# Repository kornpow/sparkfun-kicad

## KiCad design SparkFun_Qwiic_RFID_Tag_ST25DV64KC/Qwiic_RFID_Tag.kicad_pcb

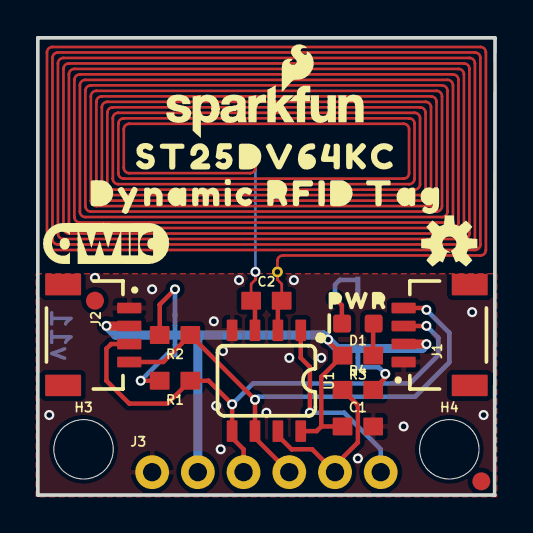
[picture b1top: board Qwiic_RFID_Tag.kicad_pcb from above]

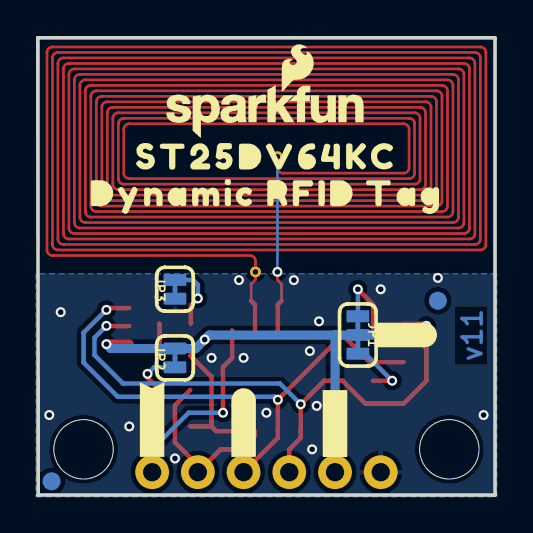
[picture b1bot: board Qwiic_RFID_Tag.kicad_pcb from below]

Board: 2 copper layers, 25.4 x 25.4 mm, 40 parts (17 on the bottom side), 13 nets.

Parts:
C1: 0.1uF; 0603
C2: 4.7pF; 0603
D1: RED; LED-0603
FD1, FD2, FD3, FD4: FIDUCIAL1X2; FIDUCIAL-1X2
FRAME2: FRAME-LETTER; CREATIVE_COMMONS
H3, H4: STAND-OFF
J1, J2: Qwiic; JST04_1MM_RA
J3: 1X06_NO_SILK
JP1: JUMPER-SMT_3_2-NC_TRACE_SILK; SMT-JUMPER_3_2-NC_TRACE_SILK
JP2, JP3: JUMPER-SMT_2_NC_TRACE_SILK; SMT-JUMPER_2_NC_TRACE_SILK
L1: PCB_4UH_INDUCTOR-1X0.5; PCB_4UH_INDUCTOR_1X0.5
LOGO1: OSHW-LOGOS; OSHW-LOGO-S
LOGO2, LOGO4: SFE_LOGO_NAME_FLAME.1_INCH; SFE_LOGO_NAME_FLAME_.1
LOGO3: QWIIC_LOGO_7MM; QWIIC_7MM
R1, R2: 2.2k; 0603
R3: 1k; 0603
R4: 10k; 0603
U1: ST25DV64KC; SO08
U$1: #I2C#0
U$3: #3V3#0
U$9: PWR11
U$10, U$11: DYNAMIC_RFID_TAG0
U$13, U$24: ST25DV64KC5984
U$16: ##GPO##9
U$17: #LED#10
U$18: #GND#4
U$20: #SDA#5
U$21: #SCL#6
U$22: ##GPO##8
U$23: #VEH#7

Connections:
3.3V: C1.1, J1.2, J2.2, J3.2, JP1.2, JP2.2, R3.2, U1.8
AC0: C2.2, L1.IN2, U1.2
AC1: C2.1, L1.IN1, U1.3
GND: C1.2, J1.1, J2.1, J3.1, JP3.1, U1.4
unnamed: D1.C, JP3.2
unnamed: JP1.3, R1.2
unnamed: JP1.1, R2.2
unnamed: D1.A, R3.1
unnamed: JP2.1, R4.2
SCL: J1.4, J2.4, J3.4, R2.1, U1.6
SDA: J1.3, J2.3, J3.3, R1.1, U1.5
VEH: J3.6, U1.1
~GPO: J3.5, R4.1, U1.7

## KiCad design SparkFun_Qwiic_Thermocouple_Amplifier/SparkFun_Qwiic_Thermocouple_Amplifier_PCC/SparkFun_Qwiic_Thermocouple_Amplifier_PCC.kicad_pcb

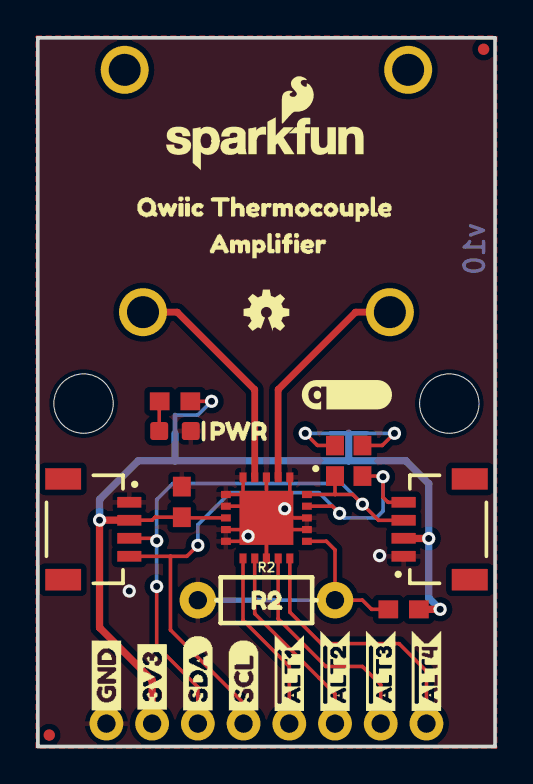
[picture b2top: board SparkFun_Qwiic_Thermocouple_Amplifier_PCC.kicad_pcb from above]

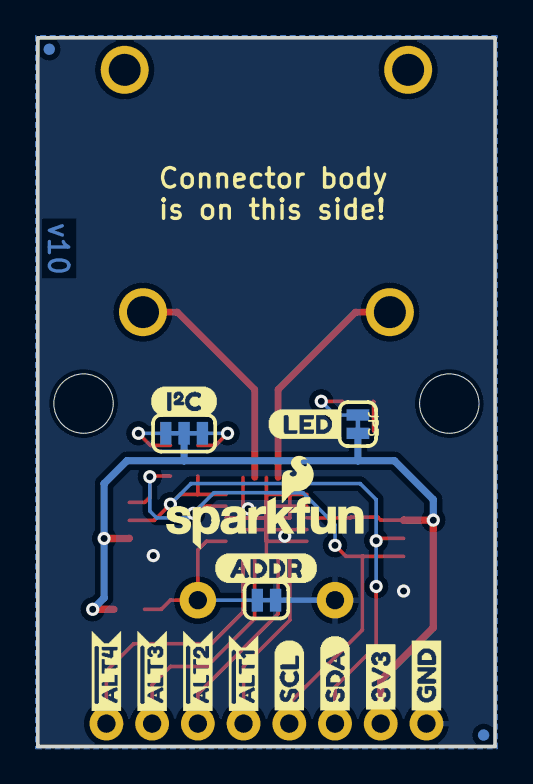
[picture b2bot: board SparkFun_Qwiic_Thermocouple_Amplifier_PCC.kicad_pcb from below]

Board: 2 copper layers, 25.4 x 39.4 mm, 50 parts (18 on the bottom side), 15 nets.

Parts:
C1: 0.1uF; 0603
D1: RED; LED-0603
FD1, FD2, FD3, FD4: FIDUCIALUFIDUCIAL; FIDUCIAL-MICRO
FRAME1: FRAME-LETTER; CREATIVE_COMMONS
J1: PTH; 1X04_NO_SILK
J2, J3: QWIIC; JST04_1MM_RA
J4: 1X04_NO_SILK
J5: PCB_THERMOCOUPLE; PCC-SMP
JP1, JP3: SMT-JUMPER_2_NC_TRACE_SILK
JP2: I2C; SMT-JUMPER_3_2-NC_TRACE_SILK
JP8, JP9: STAND-OFF
LOGO1: OSHW-LOGOMINI; OSHW-LOGO-MINI
LOGO2: SFE_LOGO_NAME_FLAME.1_INCH; SFE_LOGO_NAME_FLAME_.1
LOGO3: QWIIC_LOGO_5MM; QWIIC_5MM
R1: 1k; 0603
R2: AXIAL-0.3-KIT
R3: 10k; 0603
R4, R5: 2.2k; 0603
U1: MCP9600-SMD; MQFN-20
U$1, U$5: #ALT30
U$2: R21
U$3, U$8: #ALT10
U$4, U$18: #ALT20
U$6: QWIIC_THERMOCOUPLE2
U$7, U$11: #ALT40
U$9, U$12: SCL-[)
U$10, U$23: GND-04
U$13, U$14: SDA-[)
U$15: PWR0
U$16, U$19: 3V31
U$17: SFE_LOGO_NAME_FLAME_.1
U$20: LED0
U$21: I_SUPER2_C-()-04
U$22: ADDR1
U$25: AMPLIFIER2

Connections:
3.3V: C1.1, J1.2, J2.2, J3.2, JP2.2, JP3.2, R3.2, U1.8
ADDR: JP1.1, R2.P$2, R3.1, U1.16
GND: C1.2, D1.C, J1.1, J2.1, J3.1, JP1.2, R2.P$1, U1.1, U1.3, U1.5, U1.6, U1.7, U1.9, U1.10, U1.13, U1.17, U1.18, U1.21
unnamed: D1.A, R1.2
unnamed: JP2.1, R5.2
unnamed: JP2.3, R4.2
unnamed: J5.+, U1.2
unnamed: J5.-, U1.4
unnamed: JP3.1, R1.1
SCL: J1.4, J2.4, J3.4, R5.1, U1.19
SDA: J1.3, J2.3, J3.3, R4.1, U1.20
~ALT1: J4.1, U1.11
~ALT2: J4.2, U1.12
~ALT3: J4.3, U1.14
~ALT4: J4.4, U1.15

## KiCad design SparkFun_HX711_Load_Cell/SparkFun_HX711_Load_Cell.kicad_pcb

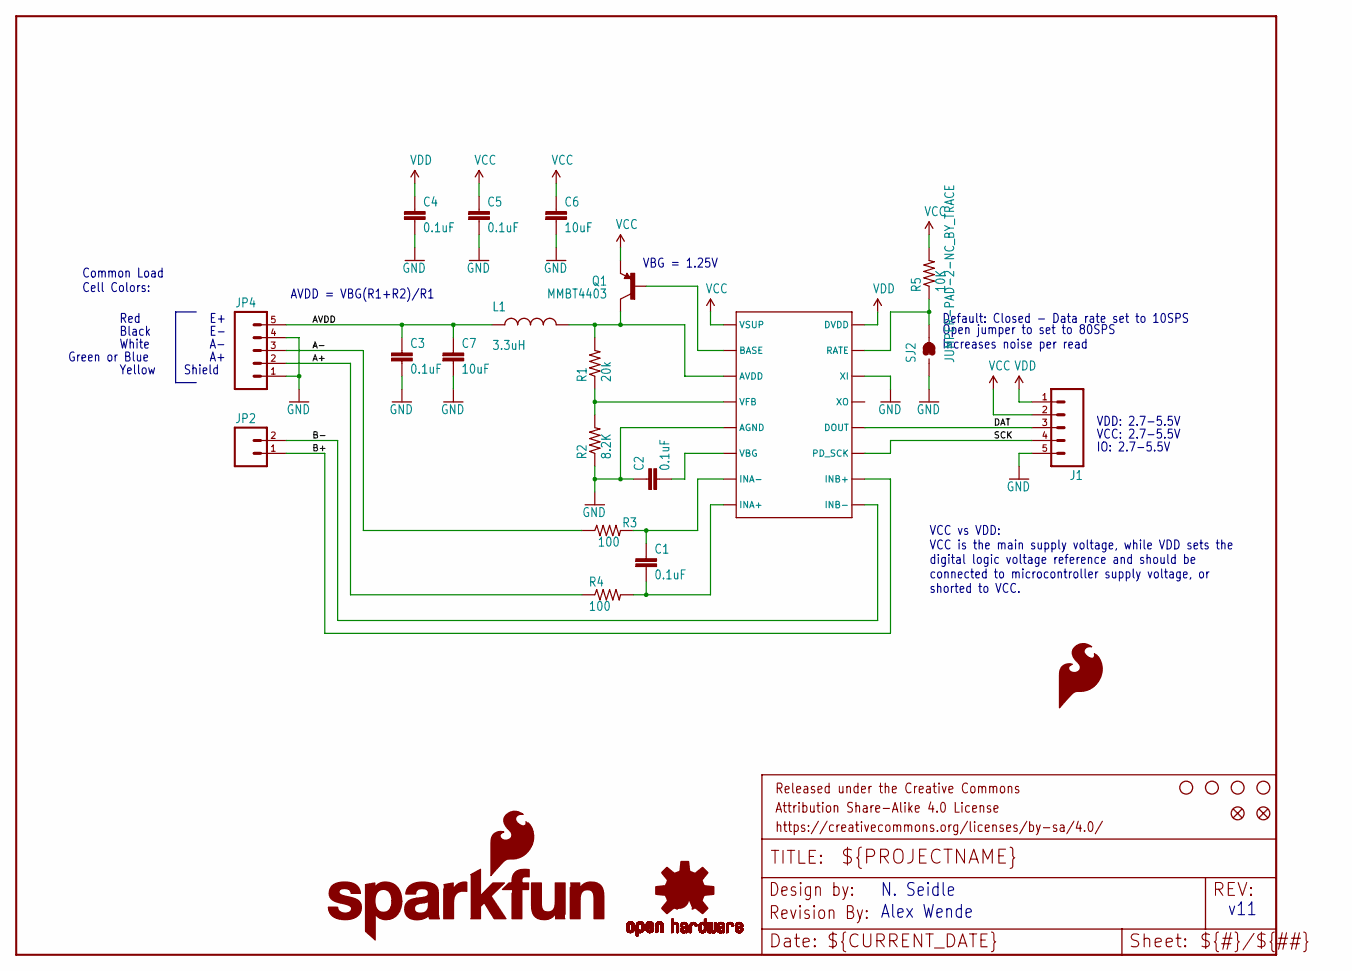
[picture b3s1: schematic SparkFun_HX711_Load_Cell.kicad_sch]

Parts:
C1, C2, C3, C4, C5: 0.1uF; 0603-CAP
C6, C7: 10uF; 1210
FID1, FID2: FIDUCIAL1X2; FIDUCIAL-1X2
FRAME1: FRAME-LETTER; CREATIVE_COMMONS
J1: M05PTH; 1X05
JP2: M02PTH; 1X02
JP4: M05PTH; 1X05
L1: 3.3uH; 0805
LOGO1: SFE_LOGO_NAME_FLAME.1_INCH; SFE_LOGO_NAME_FLAME_.1
LOGO3: SFE_LOGO_FLAME.1_INCH; SFE_LOGO_FLAME_.1
Q1: MMBT4403; SOT23-3
R1: 20k; 0603-RES
R2: 8.2K; 0603-RES
R3, R4: 100; 0603-RES
R5: 10K; 0603-RES
SJ2: JUMPER-PAD-2-NC_BY_TRACE; PAD-JUMPER-2-NC_BY_TRACE_YES_SILK
STANDOFF1, STANDOFF2, STANDOFF3, STANDOFF4: STAND-OFF
U1: HX711HX711; SO16
U7: OSHW-LOGOS; OSHW-LOGO-S
U$1: REVISION

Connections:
A+: JP4.2, R4.1
A-: JP4.3, R3.1
AVDD: C3.1, C7.1, JP4.5, L1.1
B+: JP2.1, U1.10 (INB+)
B-: JP2.2, U1.9 (INB-)
DAT: J1.3, U1.12 (DOUT)
GND: C2.1, C3.2, C4.2, C5.2, C6.2, C7.2, J1.5, JP4.1, JP4.4, R2.1, SJ2.1, U1.5 (AGND), U1.14 (XI)
unnamed: R5.1, SJ2.2, U1.15 (RATE)
unnamed: C1.1, R3.2, U1.7 (INA-)
unnamed: C1.2, R4.2, U1.8 (INA+)
unnamed: Q1.1 (B), U1.2 (BASE)
unnamed: L1.2, Q1.3 (C), R1.2, U1.3 (AVDD)
unnamed: R1.1, R2.2, U1.4 (VFB)
unnamed: C2.2, U1.6 (VBG)
SCK: J1.4, U1.11 (PD_SCK)
VCC: C5.1, C6.1, J1.2, Q1.2 (E), R5.2, U1.1 (VSUP)
VDD: C4.1, J1.1, U1.16 (DVDD)

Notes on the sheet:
Shield
Alex Wende
Common Load Cell Colors:
v11
Default: Closed - Data rate set to 10SPS
Green or Blue
White
Red
Yellow
Black
VBG = 1.25V
Open jumper to set to 80SPS Increases noise per read
VDD: 2.7-5.5V
N. Seidle
AVDD = VBG(R1+R2)/R1
VCC vs VDD: VCC is the main supply voltage, while VDD sets the digital logic voltage reference and should be connected to microcontroller supply voltage, or shorted to VCC.
IO: 2.7-5.5V
VCC: 2.7-5.5V

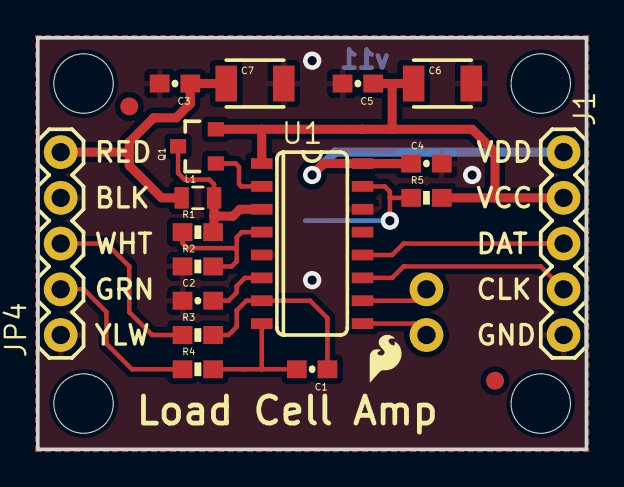
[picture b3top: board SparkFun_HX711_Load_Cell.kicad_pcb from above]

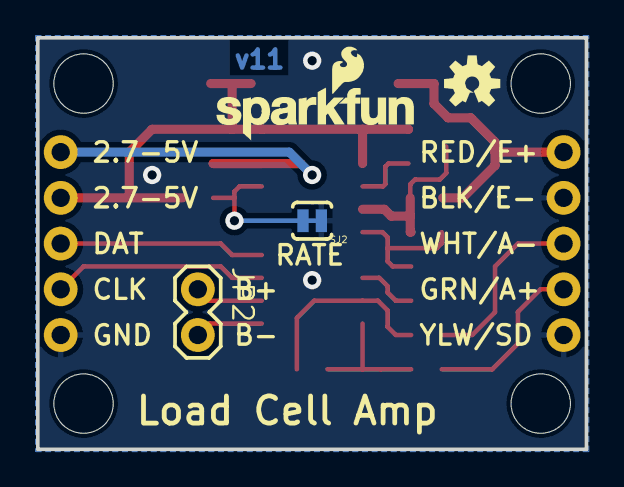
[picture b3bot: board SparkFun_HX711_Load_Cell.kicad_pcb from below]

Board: 2 copper layers, 30.5 x 22.9 mm, 30 parts (4 on the bottom side), 17 nets.

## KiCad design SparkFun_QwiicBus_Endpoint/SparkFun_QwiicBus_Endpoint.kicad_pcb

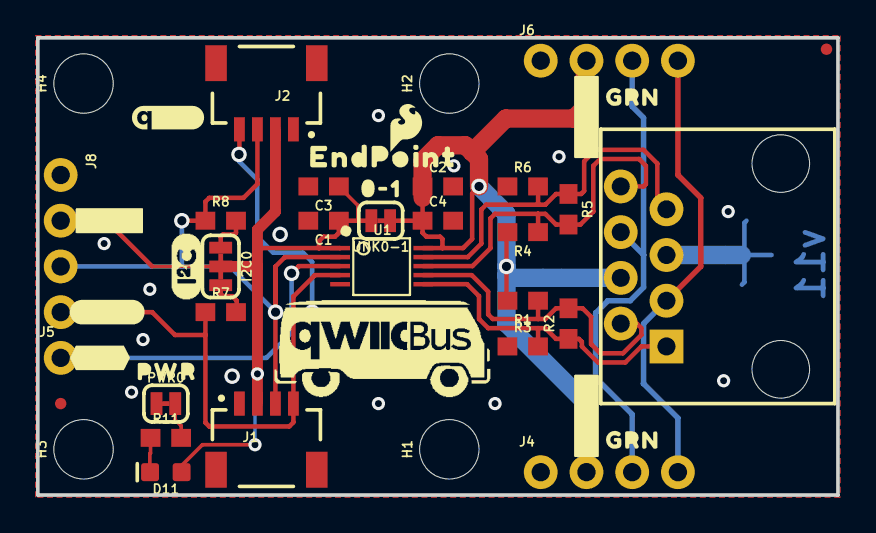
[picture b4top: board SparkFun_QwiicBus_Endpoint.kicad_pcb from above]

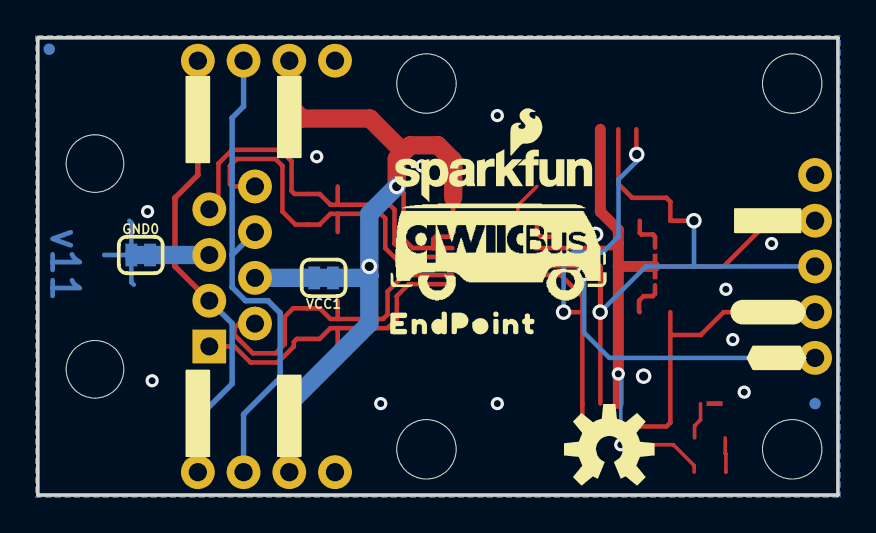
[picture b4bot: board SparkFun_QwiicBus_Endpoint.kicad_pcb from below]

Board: 2 copper layers, 44.5 x 25.4 mm, 76 parts (23 on the bottom side), 18 nets.

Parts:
C1, C2: 0.1uF; 0603
C3, C4: 1.0uF; 0603
D11: RED; LED-0603
FD1, FD2, FD3, FD4: FIDUCIALUFIDUCIAL; FIDUCIAL-MICRO
FRAME1: FRAME-LETTER; CREATIVE_COMMONS
GND0: JUMPER-SMT_2_NC_TRACE_SILK; SMT-JUMPER_2_NC_TRACE_SILK
H1, H2, H3, H4: STAND-OFF
I2C0: JUMPER-SMT_3_2-NC_TRACE_SILK; SMT-JUMPER_3_2-NC_TRACE_SILK
J1, J2: QWIIC; JST04_1MM_RA
J3: RJ45; RJ45-8
J4, J6, J8: 1X04_NO_SILK
J5: 1X01_NO_SILK
LOGO1: OSHW-LOGOM; OSHW-LOGO-M
LOGO2: REVISION
LOGO3: QWIIC_LOGO_4MM; QWIIC_4MM
LOGO4: SFE_LOGO_NAME_FLAME.1_INCH; SFE_LOGO_NAME_FLAME_.1
LOGO5: SFE_LOGO_FLAME.1_INCH; SFE_LOGO_FLAME_.1
PWR0: JUMPER-SMT_2_NC_TRACE_SILK; SMT-JUMPER_2_NC_TRACE_SILK
R1, R3, R4, R6: 390; 0603
R2, R5: 100; 0603
R7, R8: 4.7k; 0603
R11: 1k; 0603
U1: PCA9615; TSSOP10
U$1: I2C
U$2, U$29: GRN0
U$3, U$4, U$5, U$6, U$13, U$33, U$34: #GND#0
U$7, U$8: #3V3#0
U$9, U$15: #SDA#0
U$10, U$16: #SCL#0
U$11, U$17: #EN#0
U$12: #VDDA#0
U$14, U$18: #GND2#0
U$19, U$22: #GRNW#0
U$20, U$21, U$31, U$32: #VCC1#0
U$23, U$28: QWIICBUS#WORKING#LOGO#JPG
U$24, U$30: #VCC2#0
U$25: 0#10
U$26, U$35: ENDPOINT0
U$27: PWR0
UNK0-1: JUMPER-SMT_2_NC_TRACE_SILK; SMT-JUMPER_2_NC_TRACE_SILK
VCC1: JUMPER-SMT_2_NC_TRACE_SILK; SMT-JUMPER_2_NC_TRACE_SILK

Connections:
DSCL_N: J3.1, R2.1, R3.2, U1.6
DSCL_P: J3.2, R1.1, R2.2, U1.7
DSDA_N: J3.7, R5.1, R6.2, U1.9
DSDA_P: J3.8, R4.1, R5.2, U1.8
EN: J5.1, U1.3
GND: C1.2, C2.2, C3.2, C4.2, GND0.1, J1.1, J2.1, J4.1, J6.1, J8.1, PWR0.1, R3.1, R6.1, U1.5
GRN_N: J3.6, J4.3, J6.3
GRN_P: J3.3, J4.4, J6.4
unnamed: J3.4, VCC1.2
unnamed: GND0.2, J3.5
unnamed: I2C0.1, R8.2
unnamed: I2C0.3, R7.2
unnamed: D11.C, R11.1
unnamed: PWR0.2, R11.2
SCL: J1.4, J2.4, J8.4, R7.1, U1.4
SDA: J1.3, J2.3, J8.3, R8.1, U1.2
VCC: C1.1, C3.1, D11.A, I2C0.2, J1.2, J2.2, J8.2, U1.1, UNK0-1.2
VCC_1: C2.1, C4.1, J4.2, J6.2, R1.2, R4.2, U1.10, UNK0-1.1, VCC1.1

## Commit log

2024-05-28 add gitignore
2024-05-28 copy and convert QwiicBus EndPoint
    From GitHub Repo:sparkfun/SparkFun_Differential_I2C_Breakout_PCA9615_Qwiic@49600312278fdb7ca43ea27716a2875781affc55
2024-05-30 copy and convert HX711 LoadCell
    From GitHub Repo:sparkfun/HX711-Load-Cell-Amplifier/tree/V_1.1
2024-05-30 ignore backup files
2024-05-30 copy and convert Qwiic_Thermocouple_Amplifier
    From GitHub Repo:sparkfun/Qwiic_Thermocouple_Amplifer@17363932880175787ef9ed4d1c1540a5647180c7
2024-05-30 copy and convert SparkFun_Qwiic_RFID_Tag_ST25DV64KC
    From GitHub Repo:sparkfun/SparkFun_Qwiic_RFID_Tag_ST25DV64KC@3769d5a44c71c0aa3b8b94126b3d8e426dc7eeb4

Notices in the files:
SparkFun_HX711_Load_Cell/SparkFun_HX711_Load_Cell.kicad_sch:
https://creativecommons.org/licenses/by-sa/4.0
Released under the Creative Commons
parts and their libraries:
Released under the Creative Commons Attribution Share-Alike 4.0 License
